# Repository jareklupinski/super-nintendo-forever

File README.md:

# super-nintendo-forever
A Raspberry Pi Hat for controlling an SNES Sound Module using GPIO

If you want to replay the sounds of the past, nothing beats authentic hardware. This project aims to provide an easy-to-control interface between devices that can control GPIO accurately and the SNES audio module. The goal is to "play back" SNES sound data accurately through the module as if it was an actual game.

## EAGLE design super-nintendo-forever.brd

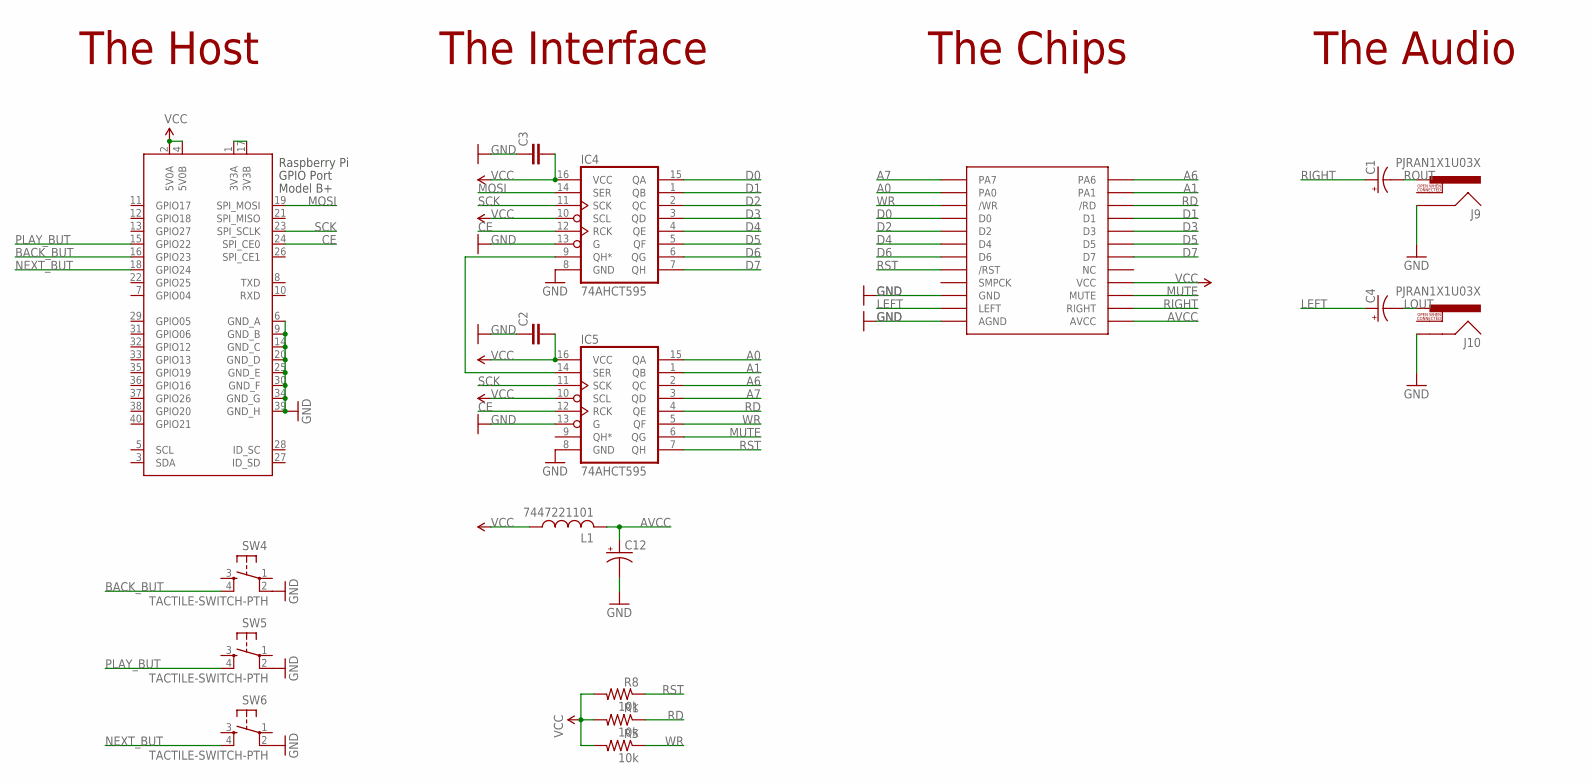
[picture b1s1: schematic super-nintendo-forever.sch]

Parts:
C1, C4, C12: CPOL-USE2-4; E2-4
C2, C3: C-EU025-024X044; C025-024X044
IC4, IC5: 74AHCT595; DIL16
J9, J10: PJRAN1X1U03X; RCA
L1: 7447221101; 12MMINDUCTOR
R1, R5, R8: 10k; 0207/7
SW4, SW5, SW6: TACTILE-SWITCH-PTH; TAC-SWITCH-PTH
U$1: APU2; APU3
X2: RASPI_BOARD_B+#_E4; RASPI_BOARD_B+_EDGES_4DRILL

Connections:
3.3V: X2.1 (3V3A), X2.17 (3V3B)
A0: IC5.15 (QA), U$1.A0
A1: IC5.1 (QB), U$1.PA1
A6: IC5.2 (QC), U$1.PA6
A7: IC5.3 (QD), U$1.A7
AVCC: C12.+, L1.3 (2), U$1.VCCA (AVCC)
BACK_BUT: SW4.4, X2.16 (GPIO23)
CE: IC4.12 (RCK), IC5.12 (RCK), X2.24 (SPI_CE0)
D0: IC4.15 (QA), U$1.D0
D1: IC4.1 (QB), U$1.D1
D2: IC4.2 (QC), U$1.D2
D3: IC4.3 (QD), U$1.D3
D4: IC4.4 (QE), U$1.D4
D5: IC4.5 (QF), U$1.D5
D6: IC4.6 (QG), U$1.D6
D7: IC4.7 (QH), U$1.D7
GND: C2.1, C3.1, C12.-, IC4.8 (GND), IC4.13 (G), IC5.8 (GND), IC5.13 (G), J9.SHELL, J10.SHELL, SW4.2, SW5.2, SW6.2, U$1.GND, U$1.GNDA (AGND), U$1.P$25 (GND), U$1.P$26 (GND), X2.6 (GND_A), X2.9 (GND_B), X2.14 (GND_C), X2.20 (GND_D), X2.25 (GND_E), X2.30 (GND_F), X2.34 (GND_G), X2.39 (GND_H)
LEFT: C4.+, U$1.OUTL (LEFT)
LOUT: C4.-, J10.PIN
MOSI: IC4.14 (SER), X2.19 (SPI_MOSI)
MUTE: IC5.6 (QG), U$1.MUTE
unnamed: IC4.9 (QH*), IC5.14 (SER)
NEXT_BUT: SW6.4, X2.18 (GPIO24)
PLAY_BUT: SW5.4, X2.15 (GPIO22)
RD: IC5.4 (QE), R1.1, U$1.!RD (/RD)
RIGHT: C1.+, U$1.OUTR (RIGHT)
ROUT: C1.-, J9.PIN
RST: IC5.7 (QH), R8.1, U$1.!RST (/RST)
SCK: IC4.11 (SCK), IC5.11 (SCK), X2.23 (SPI_SCLK)
VCC: C2.2, C3.2, IC4.10 (SCL), IC4.16 (VCC), IC5.10 (SCL), IC5.16 (VCC), L1.2 (1), R1.2, R5.2, R8.2, U$1.VCC, X2.2 (5V0A), X2.4 (5V0B)
WR: IC5.5 (QF), R5.1, U$1.!WR (/WR)

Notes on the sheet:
The Host
The Interface
The Chips
The Audio

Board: 2 copper layers, 18 parts (9 on the bottom side), 31 nets, no tracks yet.

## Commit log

2018-07-05 design untested

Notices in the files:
parts and their libraries:
SparkFun-Connectors: Licensing: Creative Commons ShareAlike 4.0 International - https://creativecommons.org/licenses/by-sa/4.0
